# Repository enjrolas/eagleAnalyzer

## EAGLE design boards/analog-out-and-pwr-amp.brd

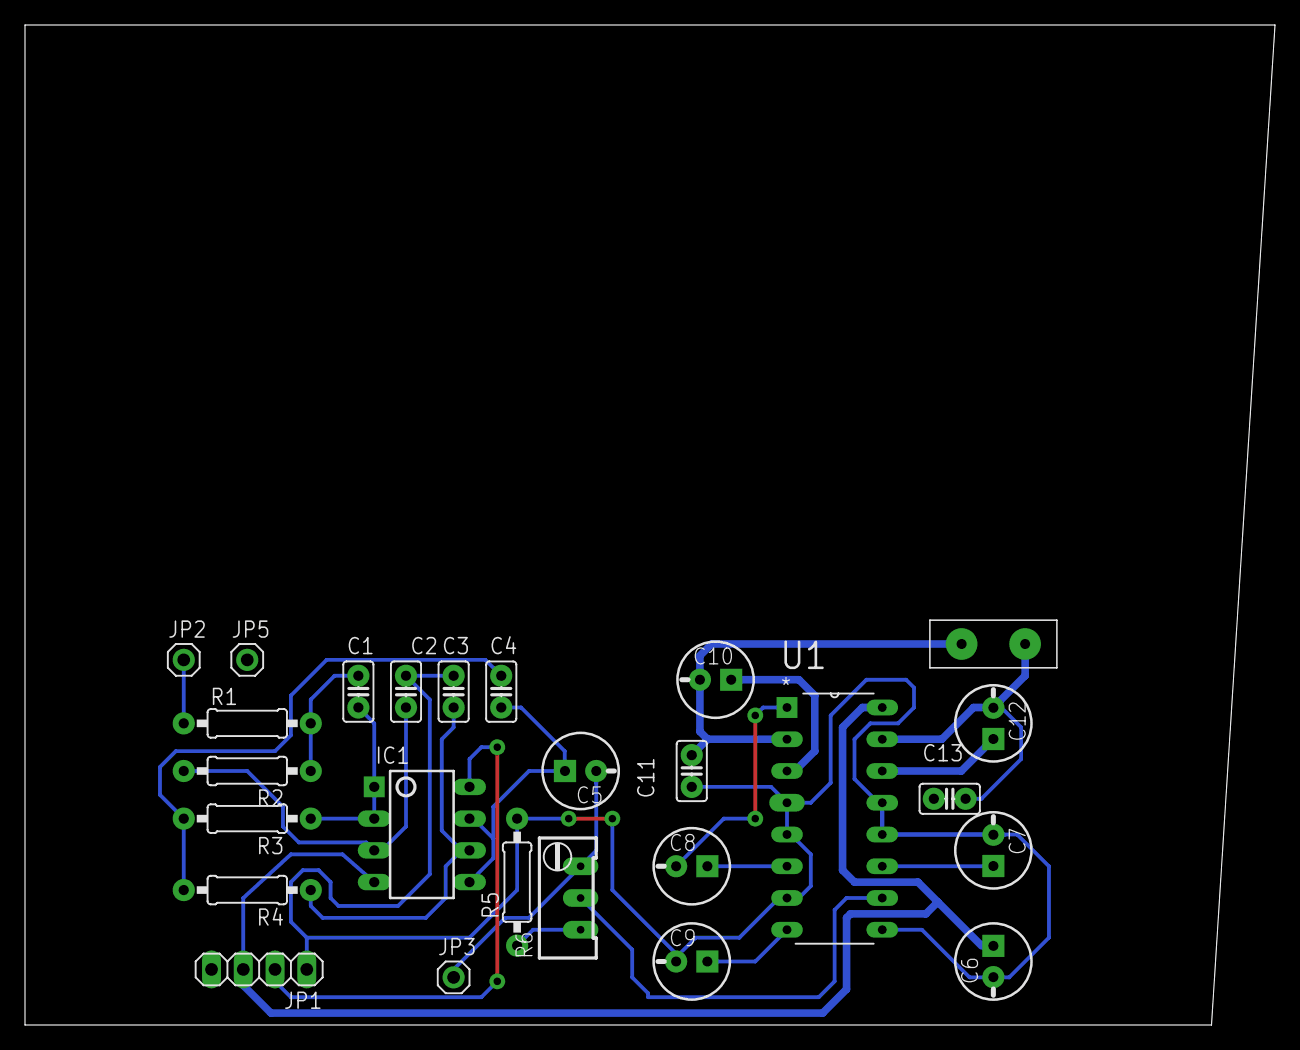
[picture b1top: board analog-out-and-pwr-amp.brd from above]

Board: 2 copper layers, 100.0 x 80.0 mm, 26 parts (0 on the bottom side), 21 nets.

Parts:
C1, C4: 223; C025-060X050
C2, C3: 222; C025-060X050
C5: POL-CAP-COMMON
C6, C7, C8, C9, C10, C12: 100uF; POL-CAP-COMMON
C11, C13: 104; C025-060X050
IC1: TL082; DIP08
JP1: 1X04
JP2, JP3, JP5: 1X01
JP4: SPEAKER; 1X02/0.5"
R1: 6.8k; R-US-COMMON
R2: 27k; R-US-COMMON
R3, R4: 1.5k; R-US-COMMON
R5: 10k; R-US-COMMON
R6: 10k; RTRIM-COMMON
U1: TEA2025B; DIP254P762X510-16

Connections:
+12V: C6.+, IC1.4, JP1.3, U1.16
-12V: IC1.8, JP1.2
GND: C2.1, C3.1, C6.-, C7.-, C9.-, C11.1, C13.1, JP1.1, JP5.1, R5.2, U1.4, U1.5, U1.7, U1.9, U1.12, U1.13
unnamed: C4.2, C5.+, IC1.5, IC1.7
unnamed: JP2.1, R1.1
unnamed: R5.1, R6.1
unnamed: C1.1, R1.2, R2.1
unnamed: C2.2, IC1.3, R2.2
unnamed: C1.2, IC1.1, IC1.2, R3.1
unnamed: C4.1, R3.2, R4.2
unnamed: C3.2, IC1.6, R4.1
unnamed: C5.-, JP3.1, R6.3
unnamed: C7.+, U1.11
unnamed: C8.+, U1.6
unnamed: C8.-, U1.1
unnamed: C12.-, C13.2, JP4.1, U1.15
unnamed: C12.+, U1.14
unnamed: C10.-, C11.2, JP4.2, U1.2
unnamed: C10.+, U1.3
unnamed: C9.+, U1.8
PWR_AMP: R6.2, U1.10

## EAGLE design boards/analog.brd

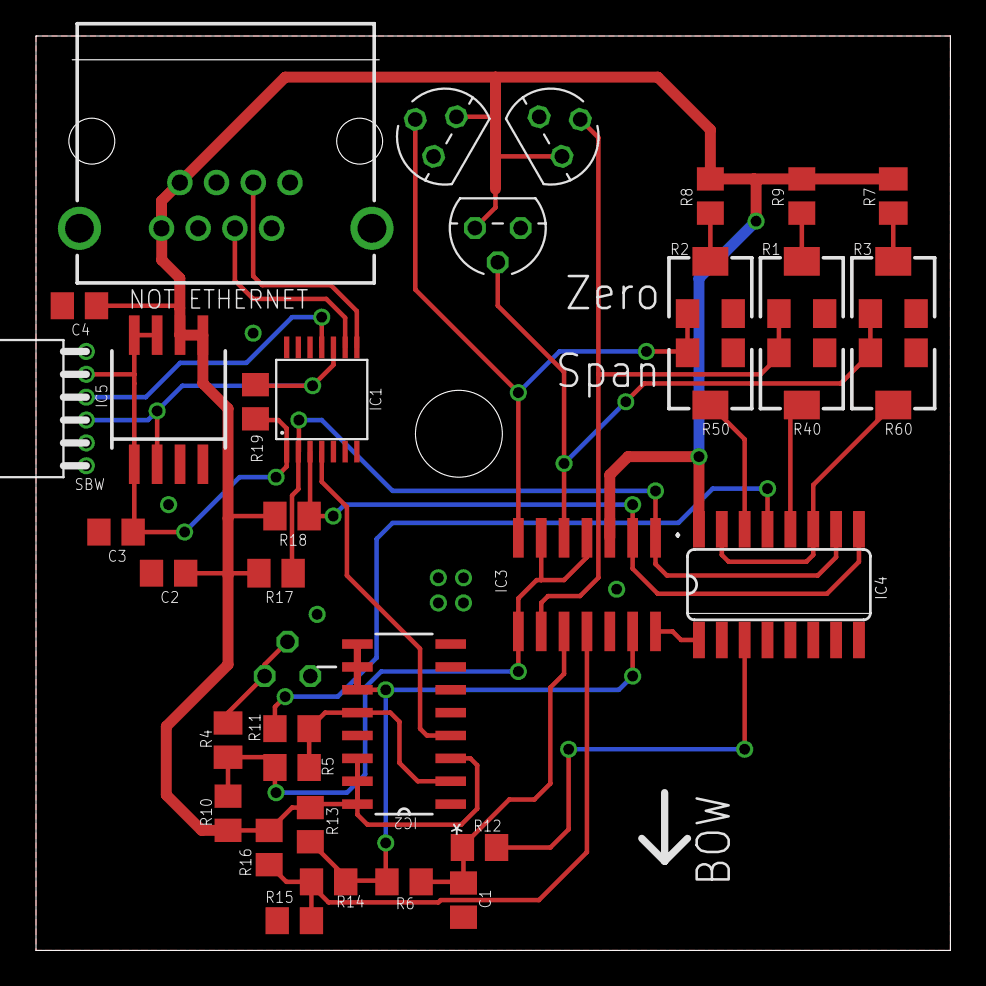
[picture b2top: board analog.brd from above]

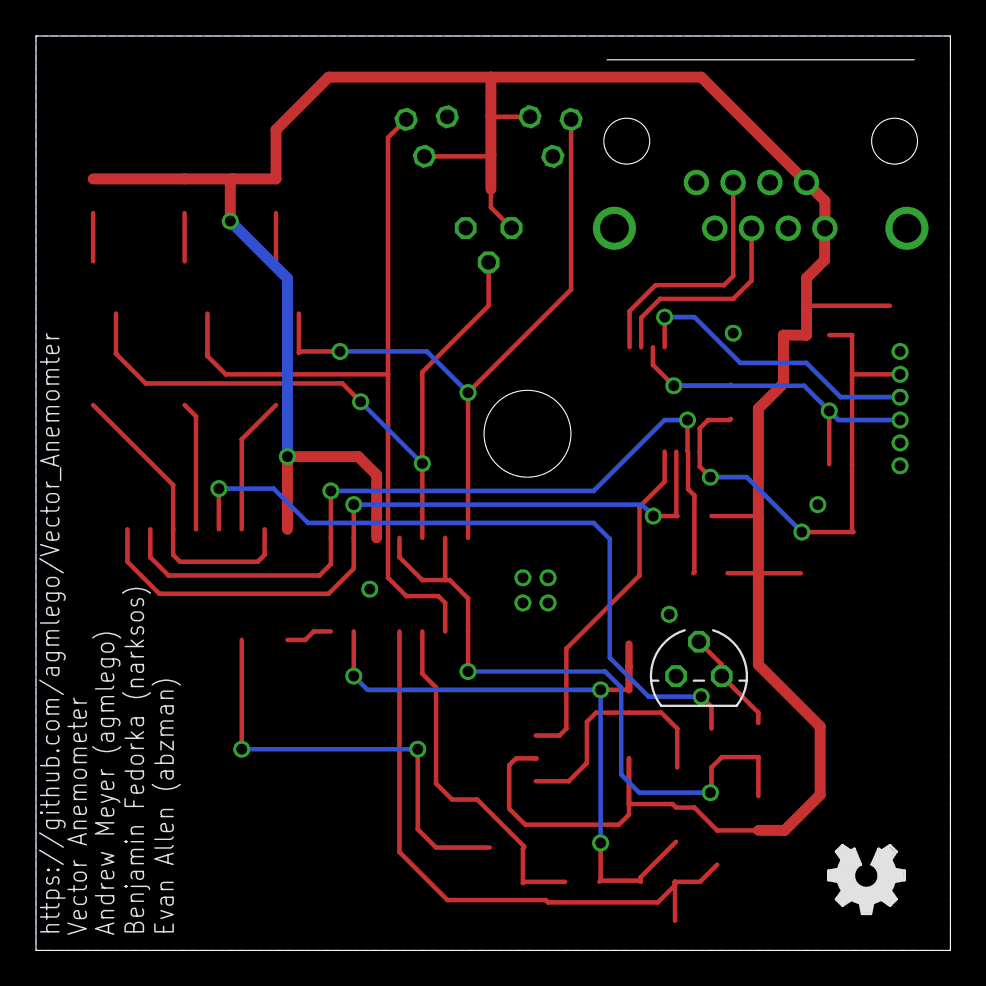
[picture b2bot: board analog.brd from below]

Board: 2 copper layers, 50.8 x 50.8 mm, 38 parts (3 on the bottom side), 28 nets.

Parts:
C1: 0.0012u; C0805
C2: 22u; C0805
C3: 10u; C0805
C4: 0.1u; C0805
IC1: G2X[2/3]1---PW14; PW14
IC2: 74HCT4053D; SOIC127P600X175-16N
IC3: LM339D; SO14
IC4: 4052D; SO16
IC5: TPS77333; SOP-08
LOGO1: OSHW_LOGO_FILLX0150-NT; OSHW_FILLX150_NOTEXT
R1, R2, R3: 20k; SM-42/43W
R4: 82; M0805
R5: 33k; R0805
R6: 220k; R0805
R7: 2.2k; M0805
R8, R9: 2.2k; R0805
R10: 12k; R0805
R11: 680; R0805
R12: 330k; R0805
R13: 3.9k; R0805
R14: 430k; R0805
R15: 620k; R0805
R16: 1.5M; R0805
R17, R18: 6.8k; M0805
R19: 47k; R0805
R40, R50, R60: 5k; SM-42/43W
SBW: 1X06
T1, T2, T3, T4: 2N3904; TO92
X1: GLX-S-88M

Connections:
AD0: IC1.2, IC3.1, IC4.10, R17.1
AD1: IC1.3, IC3.2, IC4.9, R18.1
CLK: IC1.4, IC2.4
GND: C1.2, C2.2, C3.2, C4.2, IC1.14, IC2.5, IC2.6, IC2.7, IC2.8, IC3.12, IC4.6, IC4.7, IC4.8, IC5.3, IC5.4, R15.1, SBW.5, T1.3, T2.3, T3.3, T4.3, X1.1, X1.2, X1.S1, X1.S2
unnamed: R4.1, T4.1, T4.2
unnamed: IC3.9, R1.1, R40.3, T1.2
unnamed: IC4.12, R40.2
unnamed: IC4.14, R50.2
unnamed: IC4.11, IC4.15, R60.2
unnamed: R3.2, R7.1
unnamed: R2.2, R8.1
unnamed: R1.2, R9.1
unnamed: IC3.4, IC3.6, IC3.8, R4.2, R5.1, R10.1
unnamed: IC3.5, R3.1, R60.3, T3.2
unnamed: IC3.7, R2.1, R50.3, T2.2
unnamed: IC3.14, IC4.1
unnamed: IC2.2, IC2.12, R5.2, R11.2
unnamed: IC4.13, R11.1
unnamed: IC4.3, R12.1
unnamed: C1.1, IC3.10, R6.1, R12.2
unnamed: IC2.9, IC2.10, IC2.11, IC3.13, R6.2, R13.1, R14.2
unnamed: IC3.11, R14.1, R15.2, R16.1
RST: IC1.10, IC5.2, R19.2, SBW.4
SCL: IC1.8, X1.3
SDA: IC1.9, X1.4
TEST: IC1.11, SBW.3
V33: C3.1, IC1.1, IC5.1, IC5.7, IC5.8, R19.1, SBW.2
VCC: C2.1, C4.1, IC2.3, IC2.14, IC2.15, IC2.16, IC3.3, IC4.16, IC5.5, IC5.6, R7.2, R8.2, R9.2, R10.2, R13.2, R16.2, R17.2, R18.2, T1.1, T2.1, T3.1, X1.7, X1.8

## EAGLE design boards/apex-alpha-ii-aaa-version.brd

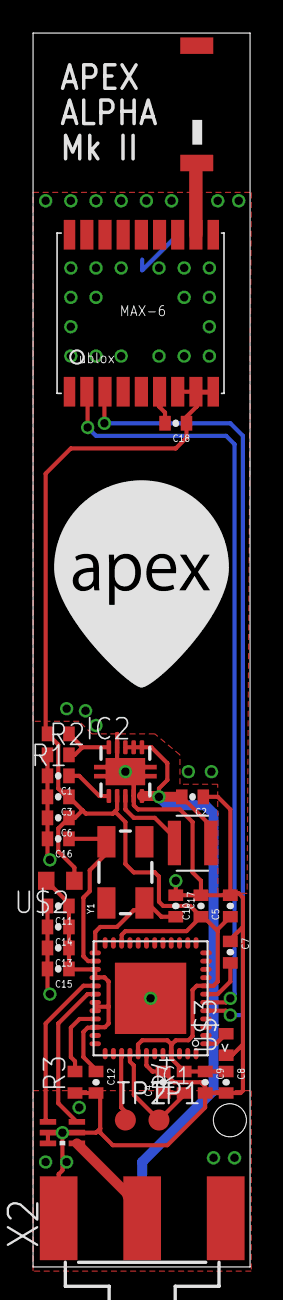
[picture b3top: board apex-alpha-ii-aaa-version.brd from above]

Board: 2 copper layers, 13.1 x 74.7 mm, 36 parts (1 on the bottom side), 20 nets.

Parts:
AAA: SMD-BATTERY-HOLDER-AAA
C1: 1uF; 0402-CAP
C2, C3, C9, C10: 10uF; 0402-CAP
C4: 2.2nF; 0402-CAP
C5, C6, C8, C11, C12, C13, C18: 100nF; 0402-CAP
C7: 470nF; 0402-CAP
C14, C15: 2pF; 0402-CAP
C16, C17: 27pF; 0402-CAP
F1: 0433BM15A0001; 2450BM15A0002
GPS: UBLOX_MAX-6
IC1: CC430F5135; RGZ48
IC2: TPS61200; S-PDSO-N10
NR3015: 2.2uH; NR3015
R1: 560k; R0402
R2: 200k; R0402
R3: 56k; R0402
R4: 47k; R0402
TP1, TP2: PTR1B1,27; B1,27
U$1: JTI_ANTENNA-1575AT43A40
U$2: EXC3BB601H; R0603
U$3: STATUS; R0402
U$4: APEXHAB-LOGO-SMALL
X2: J502-ND-142-0701-801/806
Y1: 26MHz; CRYSTAL-SMD-5X3

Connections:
GND: AAA.GND, C1.2, C2.1, C3.2, C4.2, C5.2, C6.2, C7.1, C8.2, C9.2, C10.2, C11.2, C12.2, C13.2, C14.2, C15.2, C16.2, C17.1, C18.2, F1.2, F1.5, F1.6, GPS.1_GND, GPS.6_V_BCKP, GPS.10_GND, GPS.12_GND, IC1.42, IC1.TP, IC2.4, IC2.9, IC2.PP, IC2.PP@1, IC2.PP@2, R2.1, R3.1, U$3.1, X2.G@1, X2.G@2, X2.G@3, X2.G@4
GPSRX: GPS.3_RXD1, IC1.5
GPSTX: GPS.2_TXD1, IC1.6
unnamed: AAA.+V, C2.2, IC2.5, IC2.6, IC2.7, IC2.8, NR3015.P$1
unnamed: F1.3, IC1.30
unnamed: IC2.3, NR3015.P$2
unnamed: IC2.10, R1.1, R2.2
unnamed: C1.1, IC2.1
unnamed: F1.4, IC1.29
unnamed: F1.1, X2.1
unnamed: GPS.11_RF_IN, U$1.FEED
unnamed: IC1.33, R3.2
unnamed: C7.2, IC1.7
unnamed: C4.1, IC1.40, R4.1, TP1.TP
unnamed: IC1.39, TP2.TP
unnamed: C17.2, IC1.25, Y1.1
unnamed: C16.1, IC1.26, Y1.3
unnamed: IC1.1, U$3.2
VCC: C3.1, C5.1, C6.1, C8.1, C9.1, C10.1, C18.1, GPS.7_VCC_IO, GPS.8_VCC, GPS.9_V_RESET, IC1.8, IC1.22, IC1.41, IC1.45, IC2.2, R1.2, R4.2, U$2.1
VEE: C11.1, C12.1, C13.1, C14.1, C15.1, IC1.27, IC1.28, IC1.31, IC1.32, IC1.34, U$2.2

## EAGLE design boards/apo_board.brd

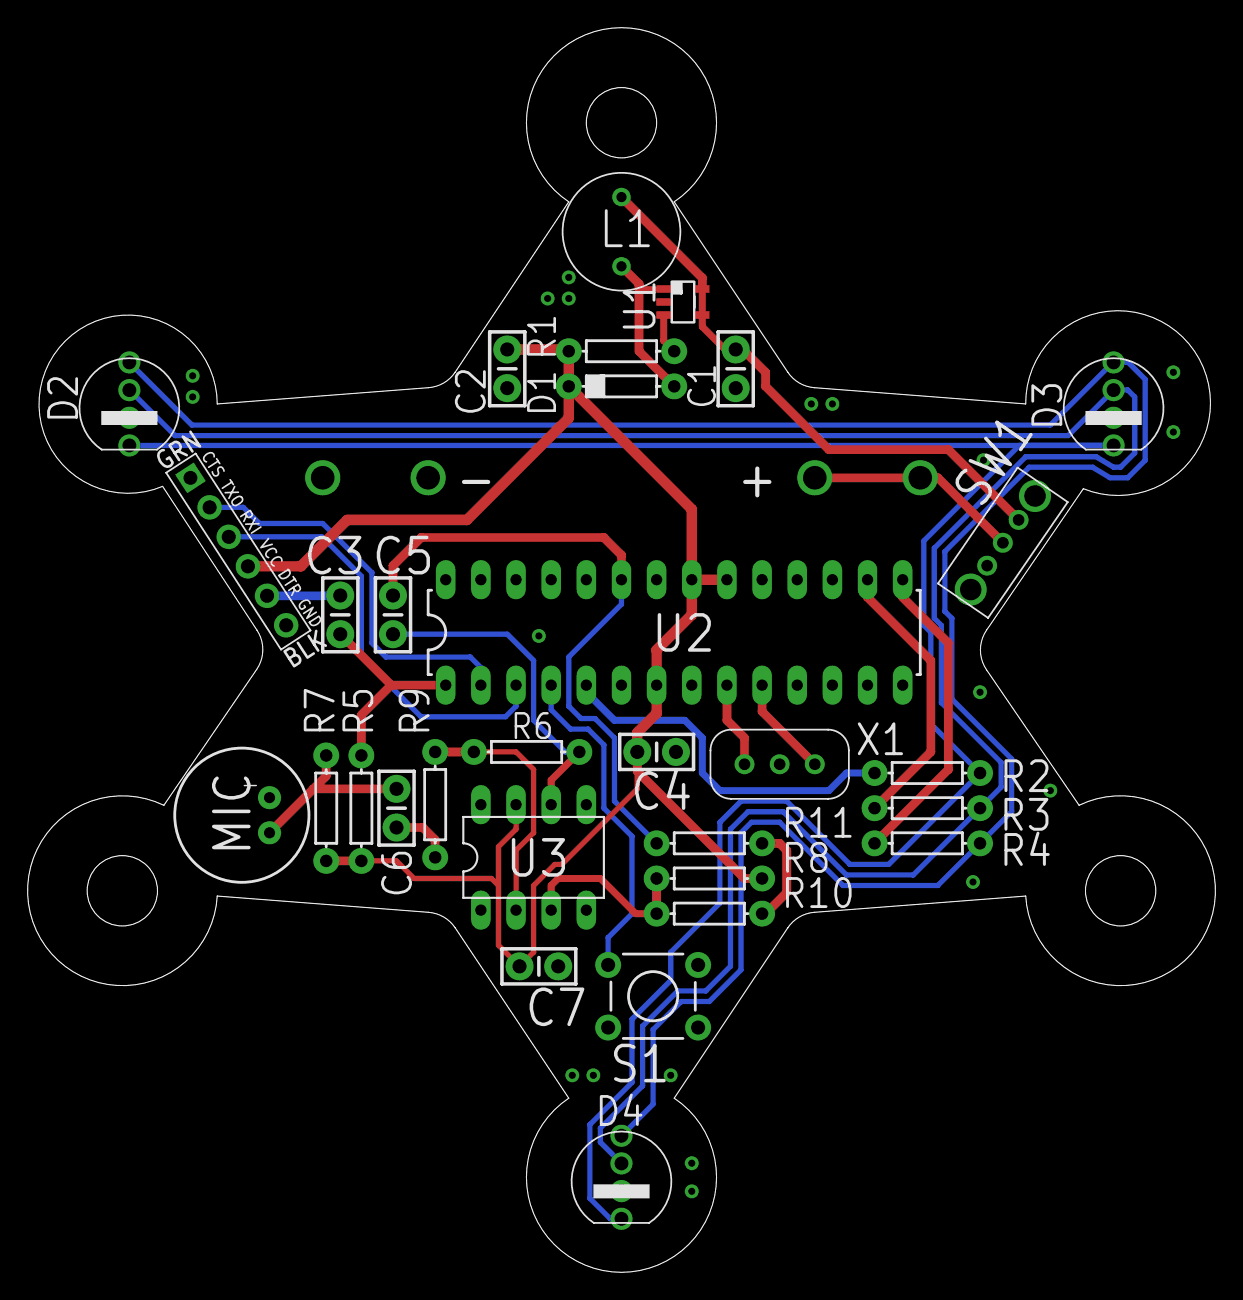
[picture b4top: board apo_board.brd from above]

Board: 2 copper layers, 85.8 x 89.9 mm, 32 parts (0 on the bottom side), 25 nets.

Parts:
BATT: BATTERY-2AAA; BATTERY-AAA
C1, C2: 22uF; CAP-PTH-SMALL-KIT
C3: 0.1uF; CAP-PTH-SMALL-KIT
C4, C5, C6, C7: 4.7uF; CAP-PTH-SMALL-KIT
D1: DIODE-1N4148
D2, D3, D4: LED-TRICOLOR-THROUGHHOLE
JP: FTDI_DEVICE; FTDI_DEVICE_SIDE
L1: 22uH; INDUCTOR_AIUR-02H
R1: 0; AXIAL-0.3
R2, R3: 250; AXIAL-0.3
R4: 1K; AXIAL-0.3
R5, R7, R8, R9, R10, R11: 20K; AXIAL-0.3
R6: 1M; AXIAL-0.3
S1: SWITCH-MOMENTARY-2PTH; TACTILE-PTH
SW1: SWITCH_SPDT; SWITCH_SPDT_OS102011MA1QN1C
U1: SP6641A; SOT23-5
U2: ATMEGA328P_PDIP; DIL28-3
U3: DIL08
U4: MIC9.7MM; MIC-9.7MM
X1: 16Mhz; CERAMIC_RESONATOR_ZTT

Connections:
+5V: C2.1, C4.1, C7.1, D1.C, JP.P$4, R1.P$2, R5.P$2, R7.P$2, R8.P$2, U2.7, U2.20, U2.21, U3.7
BATT: BATT.PWR@1, BATT.PWR@2, SW1.P$2
BLU: R3.P$1, U2.16
DTR: C3.1, JP.P$5
GND: BATT.GND@1, BATT.GND@2, C1.2, C2.2, C4.2, C7.2, D2.GND, D3.GND, D4.GND, JP.P$1, JP.P$6, R10.P$1, R11.P$1, S1.3, U1.2, U2.8, U2.22, U3.4, U4.2, X1.P$2
GRN: R4.P$1, U2.15
MIC_OUT: C5.2, R11.P$2, U2.23
unnamed: U2.9, X1.P$1
unnamed: U2.10, X1.P$3
unnamed: S1.1, U2.4
unnamed: C6.2, R9.P$2
unnamed: R8.P$1, R10.P$2, U3.3
unnamed: R6.P$2, R9.P$1, U3.2
unnamed: C6.1, R7.P$1, U4.1
unnamed: D2.GRN, D3.GRN, D4.GRN, R3.P$2
unnamed: D2.BLU, D3.BLU, D4.BLU, R4.P$2
unnamed: C3.2, R5.P$1, U2.1
unnamed: C5.1, R6.P$1, U3.6
unnamed: D2.RED, D3.RED, D4.RED, R2.P$2
unnamed: D1.A, L1.P$2, U1.1
unnamed: C1.1, L1.P$1, SW1.P$3, U1.4, U1.5
unnamed: R1.P$1, U1.3
RED: R2.P$1, U2.5
RX: JP.P$2, U2.2
TX: JP.P$3, U2.3

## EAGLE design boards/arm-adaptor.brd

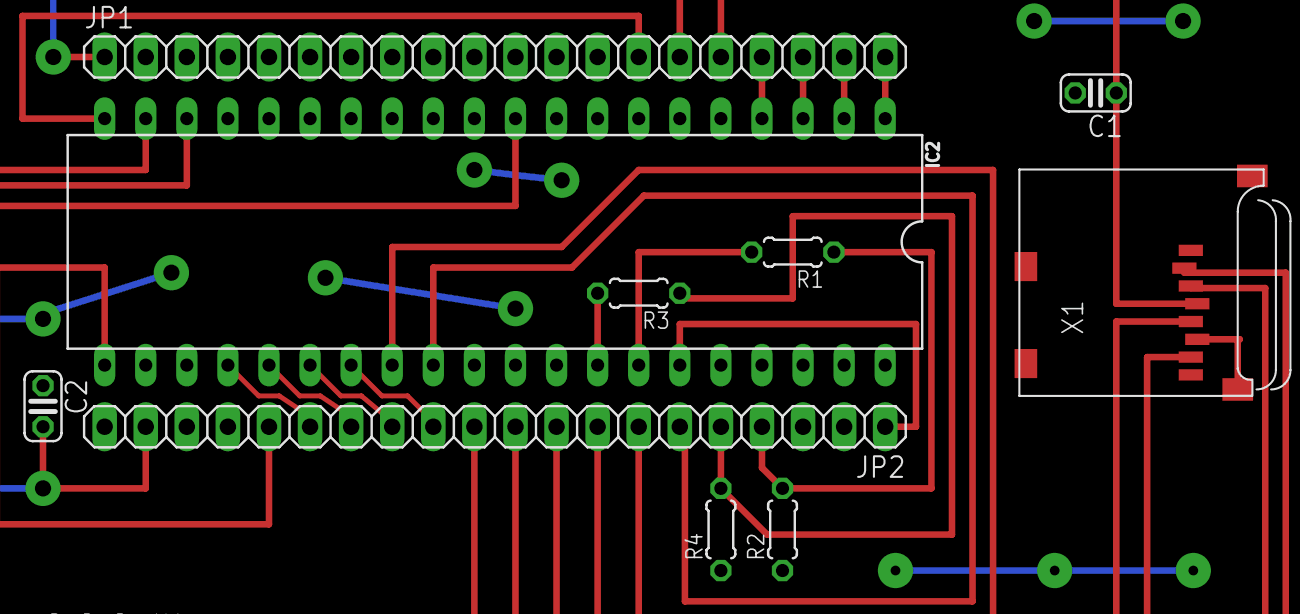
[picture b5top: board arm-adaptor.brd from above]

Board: 2 copper layers, 10 parts (0 on the bottom side), 26 nets.

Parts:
C1, C2: 0.1u; C025-024X044
IC2: ATMEGA644-20PU; DIL40
JP1, JP2: 1X20
R1, R3: 100K; 0204/5
R2, R4: 150K; 0204/5
X1: MICROSD

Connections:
!HOTBED: IC2.18, JP1.16
!HOTEND: IC2.19, JP1.15
!STEP-ENABLE: IC2.20, JP1.14
!STEP-ENABLE-Z: IC2.35, JP2.1
B-THERM: IC2.34, R1.2
CS: JP2.11, X1.2
E-DIR: IC2.1, JP1.20
E-STEP: IC2.2, JP1.19
E-THERM: IC2.33, R3.2
GND: C1.2, C2.1, IC2.11, IC2.31, JP2.20, R2.1, R4.1, X1.6, X1.MT1, X1.MT2
MISO: JP2.9, X1.7
MOSI: JP2.10, X1.3
unnamed: JP2.4, R1.1, R2.2
unnamed: JP2.5, R3.1, R4.2
SCK: JP2.8, X1.5
VDD: C1.1, JP1.1, X1.4
VIN: C2.2, IC2.10, JP2.19
X-DIR: IC2.27, JP2.12
X-STEP: IC2.21, JP2.16
X-STOP: IC2.24, JP2.15
Y-DIR: IC2.29, JP2.6
Y-STEP: IC2.28, JP2.7
Y-STOP: IC2.25, JP2.14
Z-DIR: IC2.3, JP1.18
Z-STEP: IC2.4, JP1.17
Z-STOP: IC2.26, JP2.13

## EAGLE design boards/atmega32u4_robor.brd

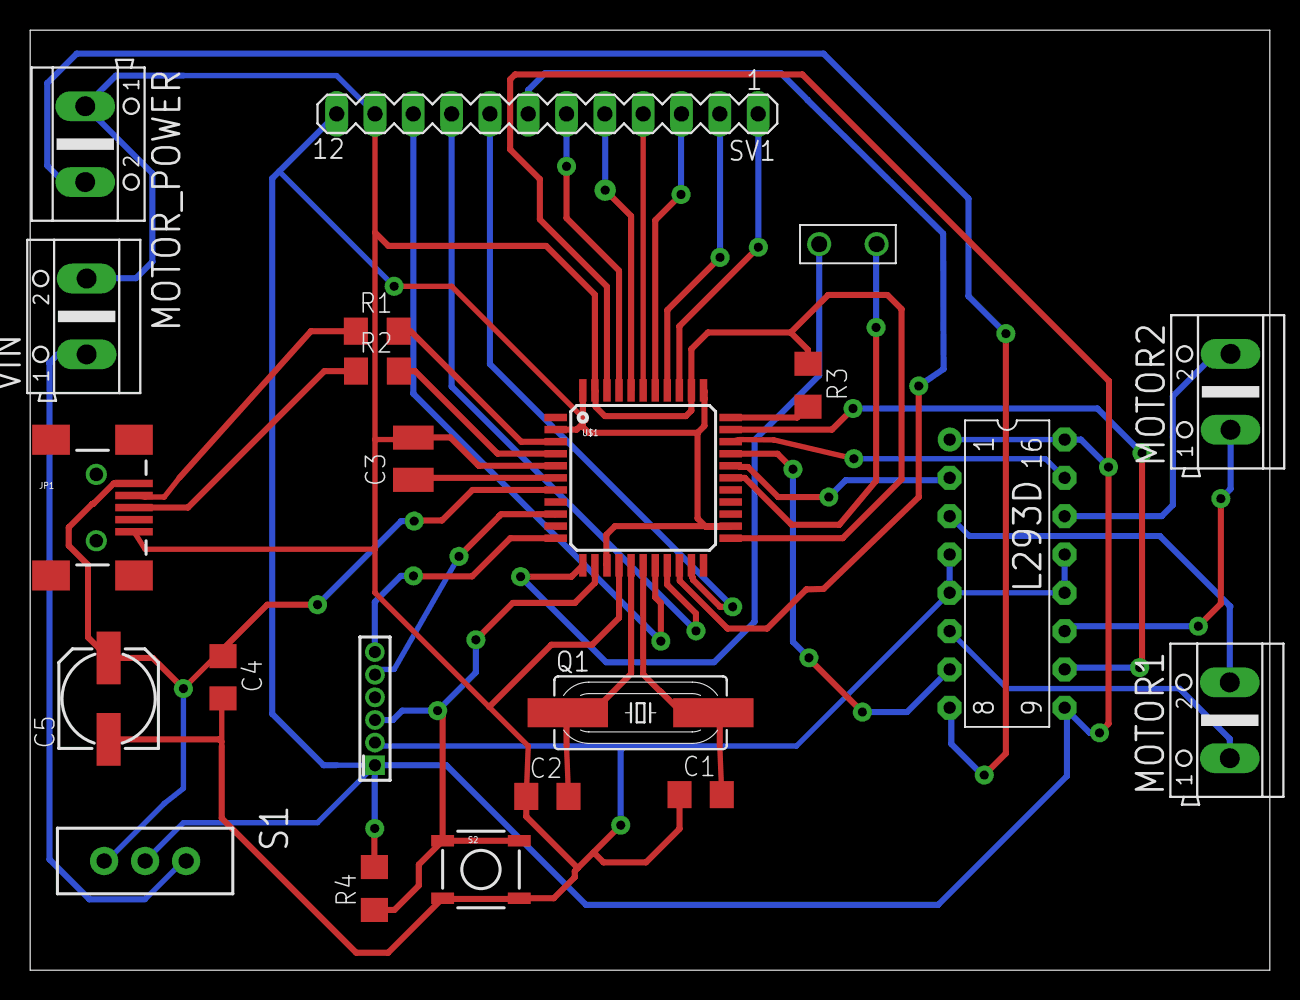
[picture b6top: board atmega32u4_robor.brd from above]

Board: 2 copper layers, 82.2 x 62.3 mm, 22 parts (0 on the bottom side), 36 nets.

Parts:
C1, C2: 22p; C1206
C3: 1uF; C1210
C4: 100n; C1206
C5: 10uF; 153CLV-0605
INT_MOTORS: 1X02_BIG
JP1: USB-SMD-NS; USB-MINIB-NOSTOP
L293D: DIL16
MOTOR1, MOTOR2: AK500/2
MOTOR_POWER: AK500/2
Q1: HC49UP
R1, R2: 22R; R1206
R3, R4: 10K; R1206
S1: SWITCH-SPDT_LOCK.007S
S2: TACTILE_SWITCH_SMD
SV1: MA12-1
U$1: ATMEGA32U4TQFP; SPARKFUN-DIGITALIC_TQFP44
U$2: AVR_MINI_PROGSMD; AVR_MINI_PROG
VIN: AK500/2

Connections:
+5V: L293D.1, L293D.9, L293D.16, R4.2, S1.2, SV1.12, U$1.2, U$1.14, U$1.24, U$1.34, U$1.42, U$1.44, U$2.1
AD1: SV1.1, U$1.36
AD2: SV1.2, U$1.37
AD3: SV1.3, U$1.38
AD4: SV1.4, U$1.39
AD5: SV1.5, U$1.40
AD6: SV1.6, U$1.41
D+: R2.2, U$1.4
D-: R1.2, U$1.3
GND: C1.1, C2.1, C3.2, C4.2, C5.-, JP1.GND, L293D.4, L293D.5, L293D.12, L293D.13, MOTOR_POWER.1, R3.1, S2.3, S2.4, SV1.11, U$1.5, U$1.15, U$1.23, U$1.35, U$1.43, U$2.2, VIN.2
INT1: INT_MOTORS.P$1, U$1.28
INT2: INT_MOTORS.P$2, U$1.12
MISO: U$1.11, U$2.6
MOTOR1_I1: L293D.2, U$1.29
MOTOR1_I2: L293D.7, U$1.30
MOTOR1_O1: L293D.3, MOTOR1.2
MOTOR1_O2: L293D.6, MOTOR1.1
MOTOR2_I1: L293D.15, U$1.31
MOTOR2_I2: L293D.10, U$1.32
MOTOR2_O1: L293D.14, MOTOR2.2
MOTOR2_O2: L293D.11, MOTOR2.1
unnamed: C1.2, Q1.2, U$1.17
unnamed: C2.2, Q1.1, U$1.16
unnamed: C3.1, U$1.6
unnamed: JP1.D-, R1.1
unnamed: JP1.D+, R2.1
unnamed: R3.2, U$1.33
unnamed: R4.1, S2.1, S2.2, U$1.13, U$2.3
RX: SV1.7, U$1.20
SCK: U$1.9, U$2.5
SCL: SV1.10, U$1.18
SDA: SV1.9, U$1.19
TX: SV1.8, U$1.21
UBUS: C4.1, C5.+, JP1.VBUS, S1.3, U$1.7
VIN: S1.1, VIN.1
VPOWER: L293D.8, MOTOR_POWER.2

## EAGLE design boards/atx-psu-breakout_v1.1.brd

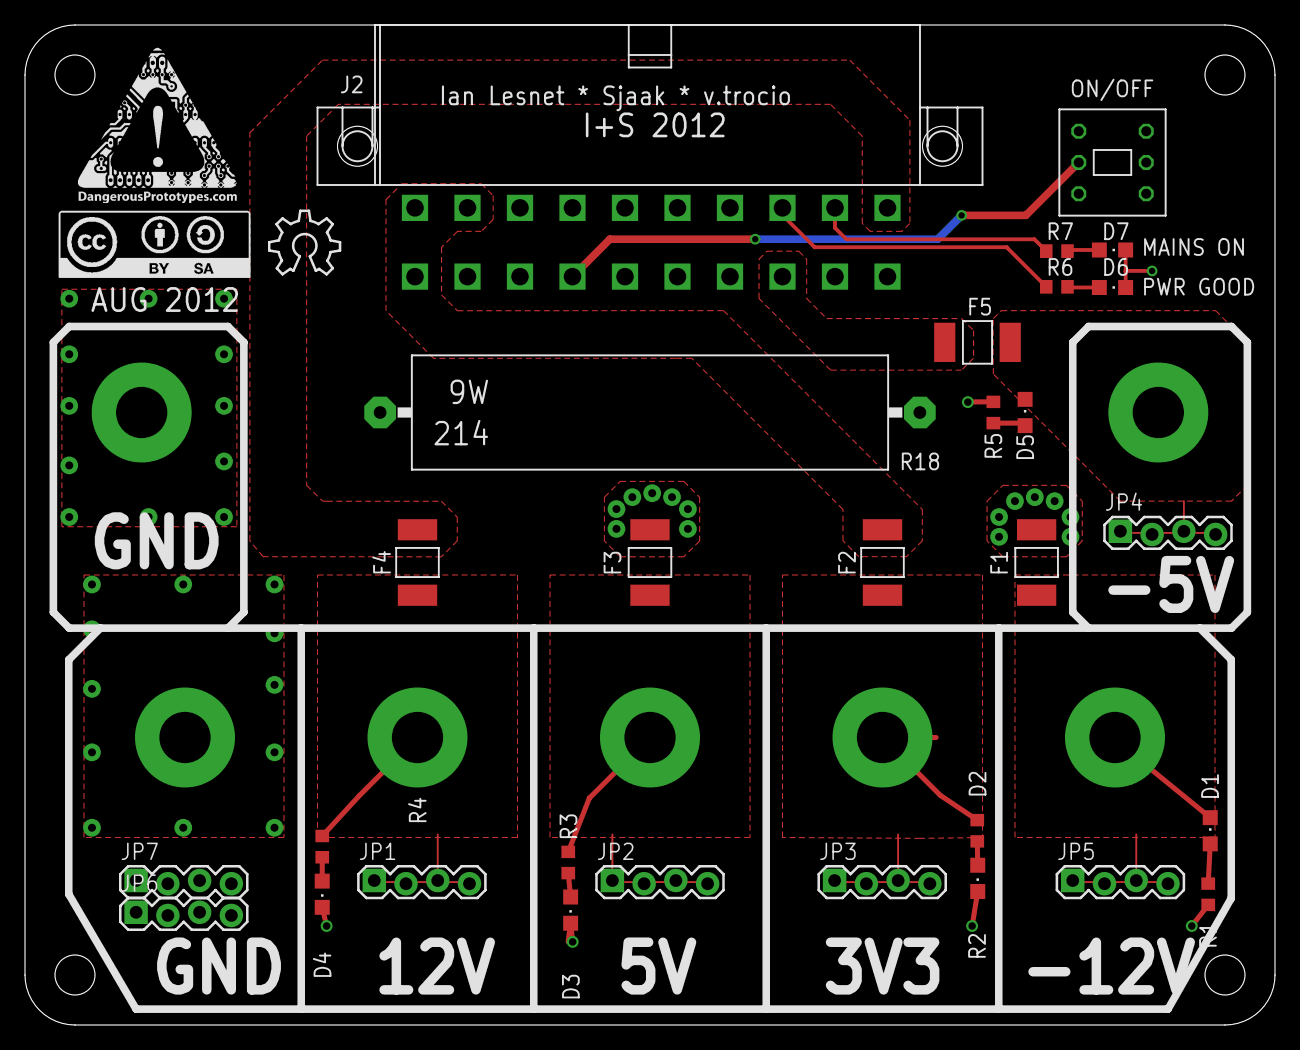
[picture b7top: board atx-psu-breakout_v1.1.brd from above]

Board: 2 copper layers, 100.0 x 80.0 mm, 41 parts (1 on the bottom side), 21 nets.

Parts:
D1, D2, D3, D4, D5, D6, D7: LED-805
F1, F2, F3, F4, F5: 2A; 1812L_PTC
J2: CON_ATX_PWR-90DEG; CON_ATX_PWR_90DEG
JP1, JP2, JP3, JP4, JP5, JP6, JP7: 1X04_LOCK
ON/OFF: SW_PUSH_DPDT; SW_PUSH_BUTTON_MINI
PCB2: PCB_DP_RECTANGLE-8X10; PCB8X10
R1, R4: 10K; R603
R2: 1.2K; R603
R3, R5, R6, R7: 3.3K; R603
R18: 10R 9W; KH214-8
T1, T2, T3, T4, T5, T6, T7: PAD_TERMINAL-4.1MMROUND; PAD_ROUND_4.1MM
U$2: DP_LOGO_ART_0.5X0.5
U$3: CC-BY-SA
U$4: OSHW_8X200_NOTEXT
U$6: LOGO_DP1.5X1.5; DP_LOGO_ART_1.5X1.5

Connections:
3V3OUT: F2.2, JP3.1, JP3.2, JP3.3, JP3.4, R2.2, T3.P
5VOUT: F3.2, JP2.1, JP2.2, JP2.3, JP2.4, R3.2, T2.P
5VSB: J2.9, R7.2
12VOUT: F4.2, JP1.1, JP1.2, JP1.3, JP1.4, R4.2, T1.P
+3V3: F2.1, J2.1, J2.2, J2.11
+5V: F3.1, J2.4, J2.6, J2.19, J2.20, R18.2
+12V: F4.1, J2.10
-5V: F5.1, J2.18
-5VOUT: D5.C, F5.2, JP4.1, JP4.2, JP4.3, JP4.4, T4.P
-12V: F1.1, J2.12
-12VOUT: D1.C, F1.2, JP5.1, JP5.2, JP5.3, JP5.4, T5.P
GND: D2.C, D3.C, D4.C, D6.C, D7.C, J2.3, J2.5, J2.7, J2.13, J2.15, J2.16, J2.17, JP6.1, JP6.2, JP6.3, JP6.4, JP7.1, JP7.2, JP7.3, JP7.4, ON/OFF.3, R1.2, R5.2, R18.1, T6.P, T7.P
unnamed: D6.A, R6.1
unnamed: D7.A, R7.1
unnamed: D4.A, R4.1
unnamed: D3.A, R3.1
unnamed: D1.A, R1.1
unnamed: D2.A, R2.1
unnamed: D5.A, R5.1
PG: J2.8, R6.2
PWR_ON: J2.14, ON/OFF.2

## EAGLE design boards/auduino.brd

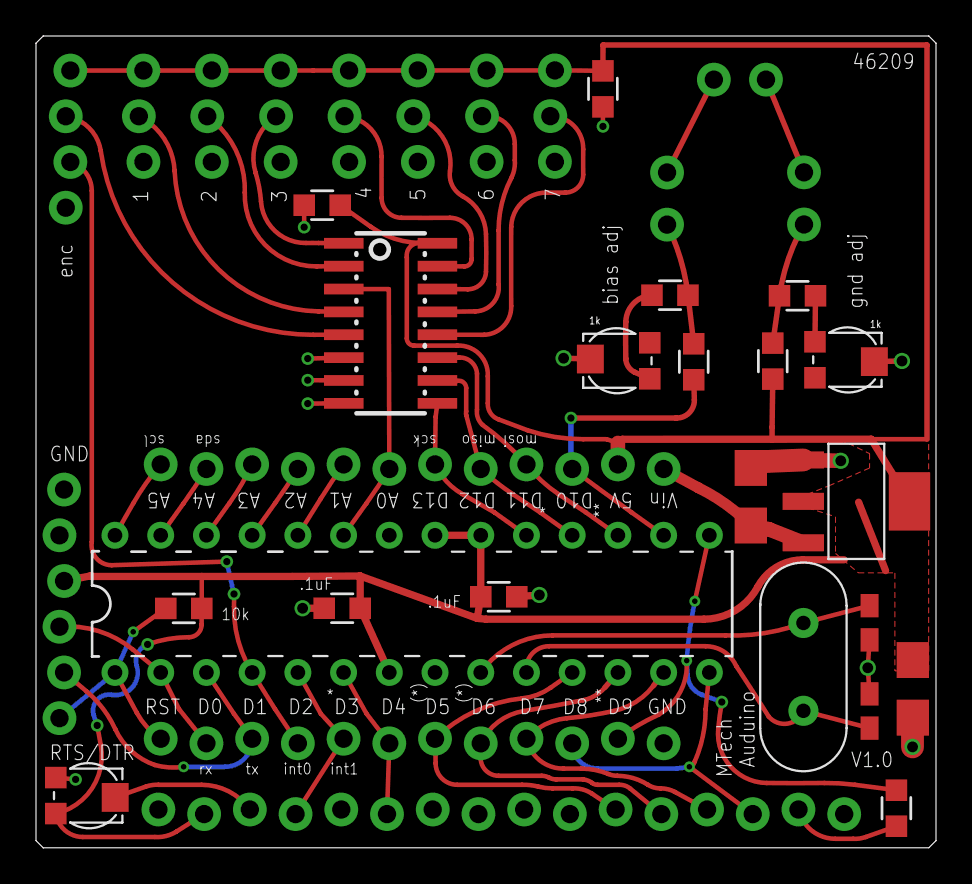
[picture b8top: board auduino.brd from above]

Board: 2 copper layers, 50.0 x 45.1 mm, 36 parts (0 on the bottom side), 42 nets.

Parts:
5V: ZLDO1117
C1, C3: 18pF; 0603-CAP
C2, C4: .1uF; 0805
C5, C8: 10uF; 1206
C6, C7: .1 uF; 0805
IC1: DIL28-3
JP1: 1X06_LOCK
JP2: M16_LOCK; 1X16_LOCK
JP3: 1X04_LOCK
JP4, JP5, JP6, JP7, JP8, JP9, JP10: 1X03_LOCK
JP11, JP12, JP13: 1X02_LOCK
R1, R3, R5: 10k; 0805
R2: 100; 0805
R4, R6: 1k; 0805
U$1: HC49US
U$2, U$5: M12; 1X12_LOCK
U$3, U$6, U$7: TRIMPOTTC33X-2; TC33X-2
U$4: NXP|HEF4051BTD; SO16

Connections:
0V5: JP12.2, R3.1, R4.2
1/10: JP11.1, R5.1, R6.2
5V: 5V.2, 5V.4, C2.2, C4.1, C5.1, C6.2, C7.1, IC1.7, IC1.20, IC1.21, JP1.4, JP2.2, JP3.1, JP4.1, JP5.1, JP6.1, JP7.1, JP8.1, JP9.1, JP10.1, R1.1, R3.2, U$3.3, U$4.16, U$5.11
A0: IC1.23, U$4.3, U$5.6
A1: IC1.24, U$5.5
A2: IC1.25, U$5.4
A3: IC1.26, U$5.3
A4: IC1.27, U$5.2
A5: IC1.28, U$5.1
CONTRAST: JP2.3, U$3.2
D0: IC1.2, JP1.3, U$2.2
D1: IC1.3, JP1.2, U$2.3
D2: IC1.4, JP3.3, U$2.4
D3: IC1.5, JP2.4, U$2.5
D4: IC1.6, JP2.6, U$2.6
D5: IC1.11, JP2.11, U$2.7
D6: IC1.12, JP2.12, U$2.8
D7: IC1.13, JP2.13, U$2.9
D8: IC1.14, JP2.14, U$2.10
D9: IC1.15, R2.2, U$2.11
D10: IC1.16, R5.2, U$5.10
D11: IC1.17, U$4.11, U$5.9
D12: IC1.18, U$4.10, U$5.8
D13: IC1.19, U$4.9, U$5.7
GND: 5V.1, C1.1, C2.1, C3.1, C4.2, C5.2, C6.1, C7.2, C8.2, IC1.8, IC1.22, JP1.5, JP1.6, JP2.1, JP2.5, JP2.16, JP3.4, JP4.3, JP5.3, JP6.3, JP7.3, JP8.3, JP9.3, JP10.3, U$2.12, U$3.1, U$4.6, U$4.7, U$4.8, U$6.2, U$7.2
LED+: JP2.15, R2.1
unnamed: R6.1, U$7.1
unnamed: JP3.2, U$4.5
unnamed: JP4.2, U$4.4
unnamed: JP5.2, U$4.2
unnamed: JP6.2, U$4.1
unnamed: JP7.2, U$4.15
unnamed: JP8.2, U$4.14
unnamed: JP9.2, U$4.13
unnamed: JP10.2, U$4.12
unnamed: R4.1, U$6.1
unnamed: JP12.1, JP13.2
unnamed: JP11.2, JP13.1
RESET: IC1.1, JP1.1, R1.2, U$2.1
VIN: 5V.3, C8.1, U$5.12
XTAL_N: C3.2, IC1.10, U$1.2
XTAL_P: C1.2, IC1.9, U$1.1

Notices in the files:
boards/arm-adaptor.brd:
Licence: GPL
parts and their libraries:
SparkFun: Licensing: CC v3.0 Share-Alike You are welcome to use this library for commercial purposes.
